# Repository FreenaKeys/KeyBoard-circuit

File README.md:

# キーボードの回路図

このリポジトリには自作キーボードの回路図データが含まれています。

## ファイル構成
- `schematic/` : 回路図ファイル (KiCad)
- `pcb/` : 基板データ
- `README.md` : この説明ファイル

## 使用方法
1. KiCad で `schematic/keyboard.sch` を開く  
2. 必要に応じて編集・出力する  

## ライセンス
今のところはありません

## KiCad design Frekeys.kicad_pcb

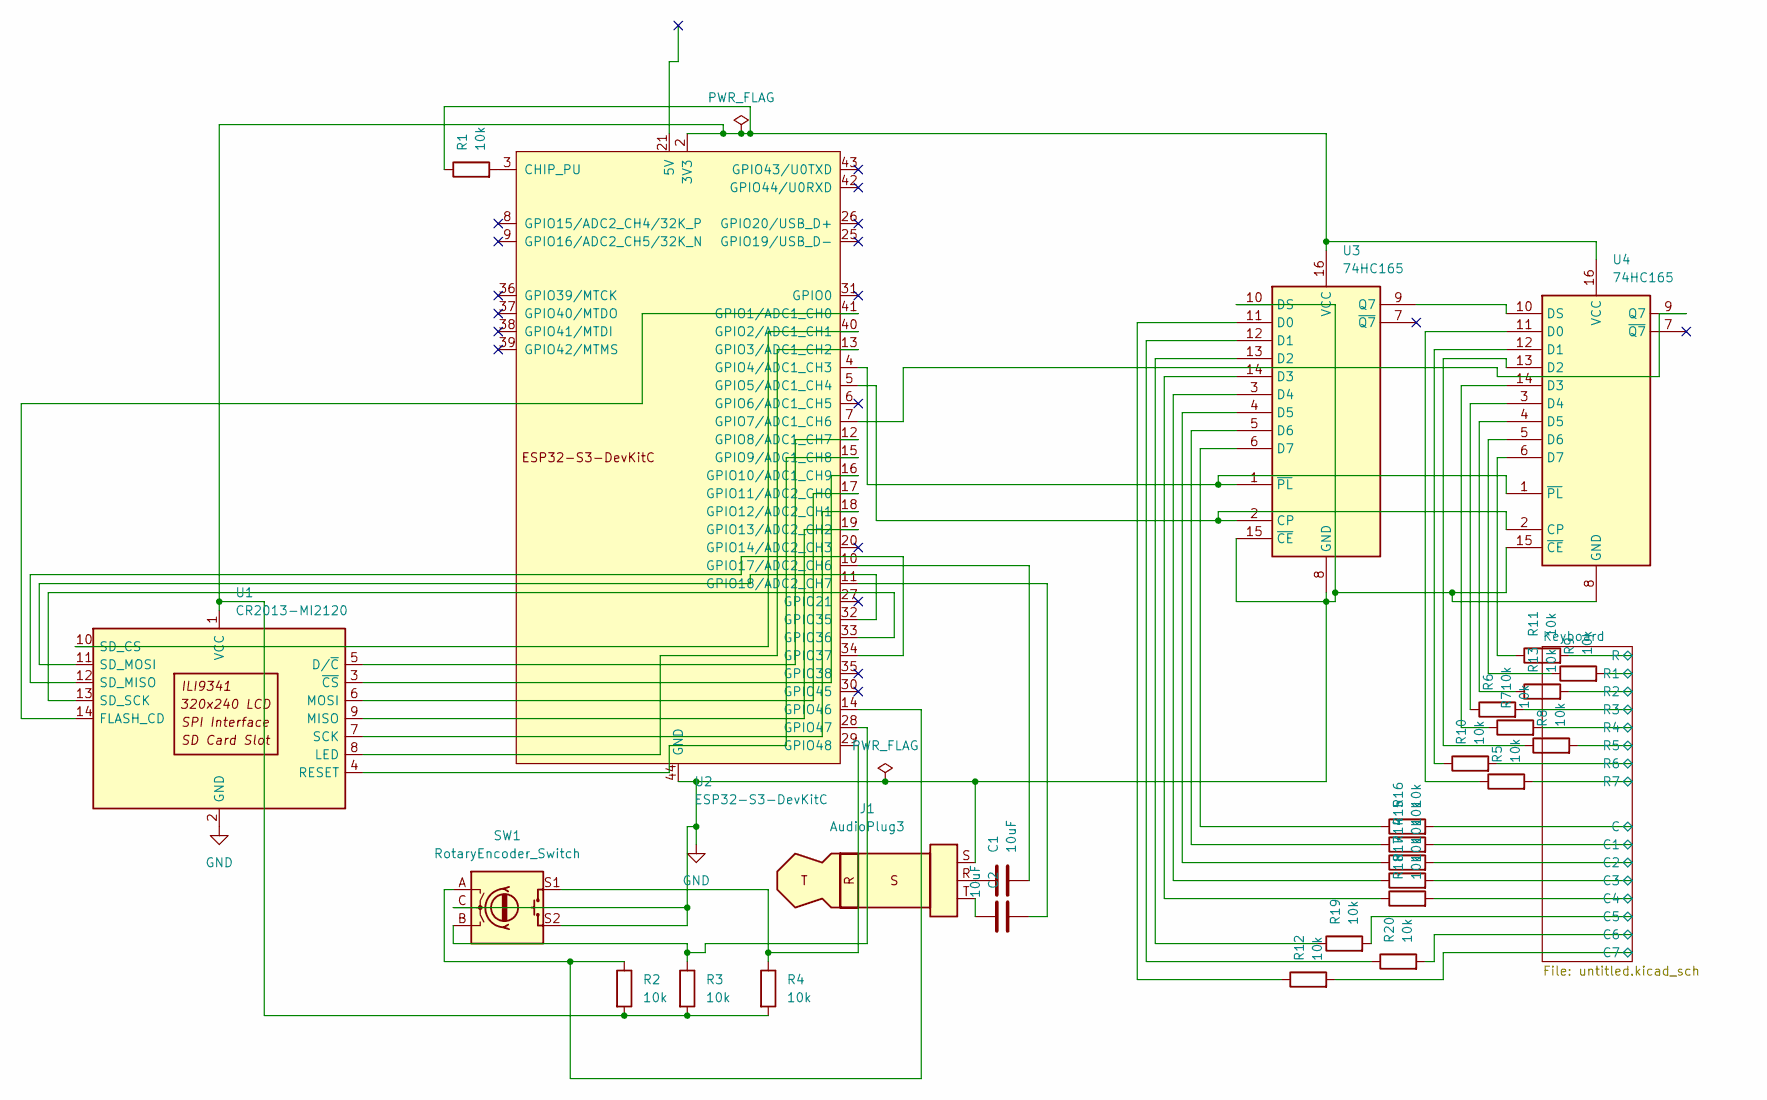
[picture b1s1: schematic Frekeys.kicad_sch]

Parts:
C1, C2: 10uF; C_0805_2012Metric
J1: AudioPlug3; Jack_3.5mm_CUI_SJ1-3523N_Horizontal
R1, R2, R3, R4, R5, R6, R7, R8, R9, R10, R11, R12, R13, R14, R15, R16, R17, R18, R19, R20: 10k; R_0805_2012Metric
SW1: RotaryEncoder_Switch; RotaryEncoder_Bourns_Vertical_PEC12R-3x17F-Sxxxx
U1: CR2013-MI2120
U2: ESP32-S3-DevKitC
U3, U4: 74HC165; SOIC-16_3.9x9.9mm_P1.27mm

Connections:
/Keyboard/C: R16.2; also elsewhere on the board
/Keyboard/C1: R15.2; also elsewhere on the board
/Keyboard/C2: R14.2; also elsewhere on the board
/Keyboard/C3: R17.2; also elsewhere on the board
/Keyboard/C4: R18.2; also elsewhere on the board
/Keyboard/C5: R19.2; also elsewhere on the board
/Keyboard/C6: R20.2; also elsewhere on the board
/Keyboard/C7: R12.2; also elsewhere on the board
/Keyboard/R: R11.2; also elsewhere on the board
/Keyboard/R1: R9.2; also elsewhere on the board
/Keyboard/R2: R13.2; also elsewhere on the board
/Keyboard/R3: R6.2; also elsewhere on the board
/Keyboard/R4: R7.2; also elsewhere on the board
/Keyboard/R5: R8.2; also elsewhere on the board
/Keyboard/R6: R10.2; also elsewhere on the board
/Keyboard/R7: R5.2; also elsewhere on the board
GND: J1.S, SW1.C, SW1.S2, U1.2 (GND), U2.22 (GND), U2.23 (GND), U2.24 (GND), U2.44 (GND), U3.8 (GND), U3.10 (DS), U3.15 (~CE), U4.8 (GND), U4.15 (~CE)
unnamed: C1.1, J1.R
unnamed: C2.1, J1.T
unnamed: U1.5 (D/~C), U2.12 (GPIO8/ADC1_CH7)
unnamed: U1.14 (FLASH_CD), U2.41 (GPIO1/ADC1_CH0)
unnamed: U1.8 (LED), U2.13 (GPIO3/ADC1_CH2)
unnamed: U1.9 (MISO), U2.19 (GPIO13/ADC2_CH2)
unnamed: U1.6 (MOSI), U2.17 (GPIO11/ADC2_CH0)
unnamed: U1.4 (RESET), U2.15 (GPIO9/ADC1_CH8)
unnamed: U1.7 (SCK), U2.18 (GPIO12/ADC2_CH1)
unnamed: U1.10 (SD_CS), U2.40 (GPIO2/ADC1_CH1)
unnamed: U1.12 (SD_MISO), U2.34 (GPIO37)
unnamed: U1.11 (SD_MOSI), U2.32 (GPIO35)
unnamed: U1.13 (SD_SCK), U2.33 (GPIO36)
unnamed: R1.1, R2.2, R3.2, R4.2, U1.1 (VCC), U2.1 (3V3), U2.2 (3V3), U3.16 (VCC), U4.16 (VCC)
unnamed: U1.3 (~CS), U2.16 (GPIO10/ADC1_CH9)
unnamed: R1.2, U2.3 (CHIP_PU)
unnamed: U2.4 (GPIO4/ADC1_CH3), U3.1 (~PL), U4.1 (~PL)
unnamed: U2.5 (GPIO5/ADC1_CH4), U3.2 (CP), U4.2 (CP)
unnamed: U2.7 (GPIO7/ADC1_CH6), U4.9 (Q7)
unnamed: C1.2, U2.10 (GPIO17/ADC2_CH6)
unnamed: C2.2, U2.11 (GPIO18/ADC2_CH7)
unnamed: R2.1, SW1.A, U2.14 (GPIO46)
unnamed: R3.1, SW1.B, U2.28 (GPIO47)
unnamed: R4.1, SW1.S1, U2.29 (GPIO48)
unnamed: R12.1, U3.11 (D0)
unnamed: R20.1, U3.12 (D1)
unnamed: R19.1, U3.13 (D2)
unnamed: R18.1, U3.14 (D3)
unnamed: R17.1, U3.3 (D4)
unnamed: R14.1, U3.4 (D5)
unnamed: R15.1, U3.5 (D6)
unnamed: R16.1, U3.6 (D7)
unnamed: U3.9 (Q7), U4.10 (DS)
unnamed: R5.1, U4.11 (D0)
unnamed: R10.1, U4.12 (D1)
unnamed: R8.1, U4.13 (D2)
unnamed: R7.1, U4.14 (D3)
unnamed: R6.1, U4.3 (D4)
unnamed: R13.1, U4.4 (D5)
unnamed: R9.1, U4.5 (D6)
unnamed: R11.1, U4.6 (D7)

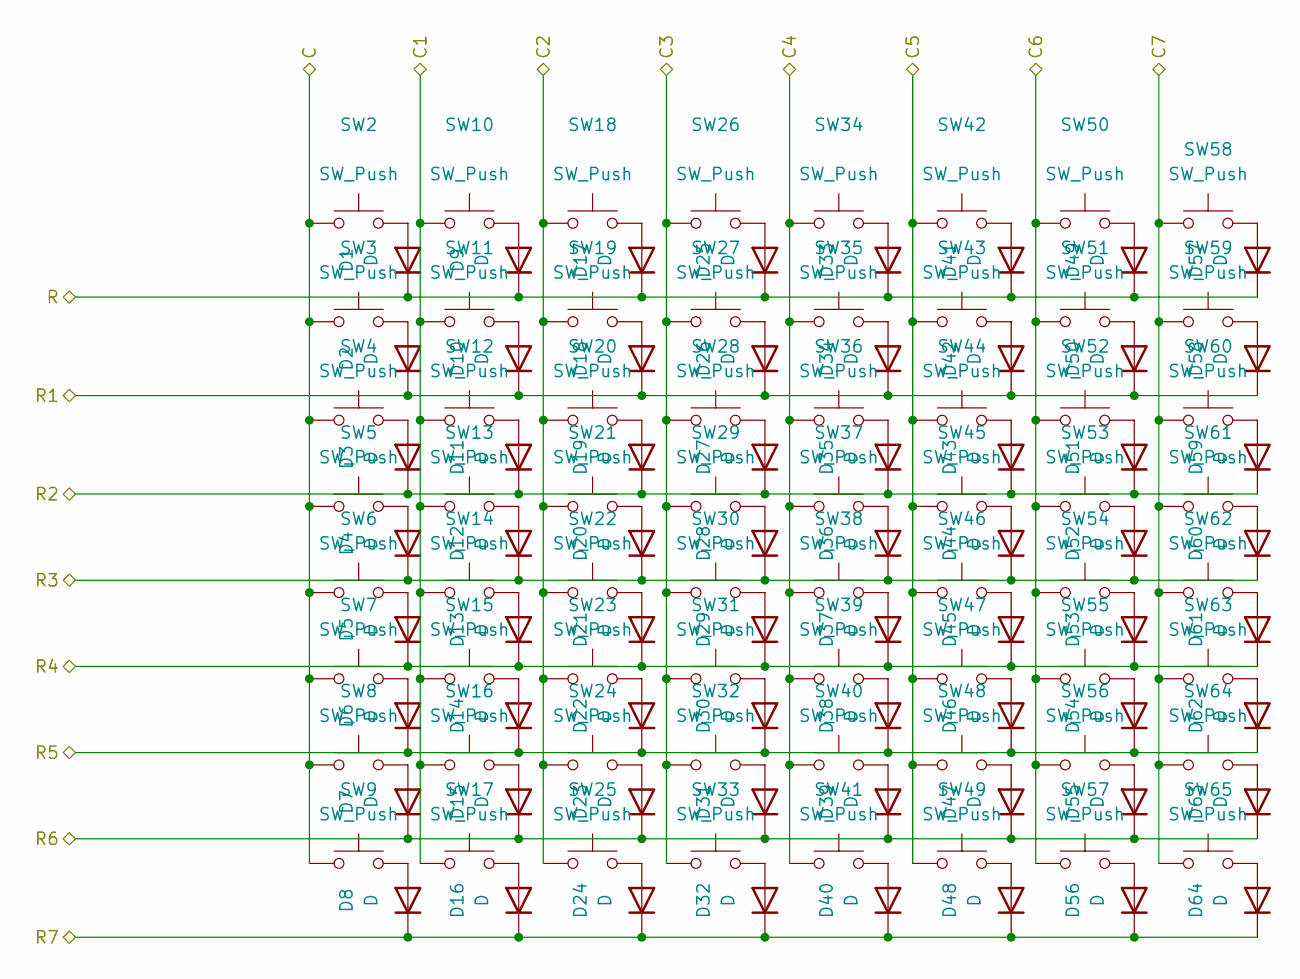
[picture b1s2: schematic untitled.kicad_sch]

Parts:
D1, D2, D3, D4, D5, D6, D7, D8, D9, D10, D11, D12, D13, D14, D15, D16, D17, D18, D19, D20, D21, D22, D23, D24, D25, D26, D27, D28, D29, D30, D31, D32, D33, D34, D35, D36, D37, D38, D39, D40, D41, D42, D43, D44, D45, D46, D47, D48, D49, D50, D51, D52, D53, D54, D55, D56, D57, D58, D59, D60, D61, D62, D63, D64: D; D_0805_2012Metric
SW2, SW7, SW8, SW9, SW10, SW11, SW12, SW13, SW15, SW16, SW17, SW18, SW19, SW20, SW21, SW23, SW24, SW25, SW26, SW27, SW28, SW29, SW30, SW31, SW32, SW33, SW34, SW35, SW36, SW37, SW39, SW40, SW41, SW42, SW43, SW44, SW45, SW46, SW47, SW48, SW49, SW50, SW51, SW52, SW53, SW54, SW55, SW56, SW57, SW58, SW59, SW60, SW61, SW62, SW65: SW_Push; SW_Hotswap_Kailh_MX_1.00u
SW3: SW_Push; SW_Hotswap_Kailh_MX_1.50u
SW4: SW_Push; SW_Hotswap_Kailh_MX_1.75u
SW5, SW63: SW_Push; SW_Hotswap_Kailh_MX_2.00u
SW6, SW14, SW22: SW_Push; SW_Hotswap_Kailh_MX_1.25u
SW38: SW_Push; SW_Hotswap_Kailh_MX_6.25u
SW64: SW_Push; SW_Hotswap_Kailh_MX_ISOEnter

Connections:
/Keyboard/C: SW2.1, SW3.1, SW4.1, SW5.1, SW6.1, SW7.1, SW8.1, SW9.1; also elsewhere on the board
/Keyboard/C1: SW10.1, SW11.1, SW12.1, SW13.1, SW14.1, SW15.1, SW16.1, SW17.1; also elsewhere on the board
/Keyboard/C2: SW18.1, SW19.1, SW20.1, SW21.1, SW22.1, SW23.1, SW24.1, SW25.1; also elsewhere on the board
/Keyboard/C3: SW26.1, SW27.1, SW28.1, SW29.1, SW30.1, SW31.1, SW32.1, SW33.1; also elsewhere on the board
/Keyboard/C4: SW34.1, SW35.1, SW36.1, SW37.1, SW38.1, SW39.1, SW40.1, SW41.1; also elsewhere on the board
/Keyboard/C5: SW42.1, SW43.1, SW44.1, SW45.1, SW46.1, SW47.1, SW48.1, SW49.1; also elsewhere on the board
/Keyboard/C6: SW50.1, SW51.1, SW52.1, SW53.1, SW54.1, SW55.1, SW56.1, SW57.1; also elsewhere on the board
/Keyboard/C7: SW58.1, SW59.1, SW60.1, SW61.1, SW62.1, SW63.1, SW64.1, SW65.1; also elsewhere on the board
/Keyboard/R: D1.1 (K), D9.1 (K), D17.1 (K), D25.1 (K), D33.1 (K), D41.1 (K), D49.1 (K), D57.1 (K); also elsewhere on the board
/Keyboard/R1: D2.1 (K), D10.1 (K), D18.1 (K), D26.1 (K), D34.1 (K), D42.1 (K), D50.1 (K), D58.1 (K); also elsewhere on the board
/Keyboard/R2: D3.1 (K), D11.1 (K), D19.1 (K), D27.1 (K), D35.1 (K), D43.1 (K), D51.1 (K), D59.1 (K); also elsewhere on the board
/Keyboard/R3: D4.1 (K), D12.1 (K), D20.1 (K), D28.1 (K), D36.1 (K), D44.1 (K), D52.1 (K), D60.1 (K); also elsewhere on the board
/Keyboard/R4: D5.1 (K), D13.1 (K), D21.1 (K), D29.1 (K), D37.1 (K), D45.1 (K), D53.1 (K), D61.1 (K); also elsewhere on the board
/Keyboard/R5: D6.1 (K), D14.1 (K), D22.1 (K), D30.1 (K), D38.1 (K), D46.1 (K), D54.1 (K), D62.1 (K); also elsewhere on the board
/Keyboard/R6: D7.1 (K), D15.1 (K), D23.1 (K), D31.1 (K), D39.1 (K), D47.1 (K), D55.1 (K), D63.1 (K); also elsewhere on the board
/Keyboard/R7: D8.1 (K), D16.1 (K), D24.1 (K), D32.1 (K), D40.1 (K), D48.1 (K), D56.1 (K), D64.1 (K); also elsewhere on the board
unnamed: D1.2 (A), SW2.2
unnamed: D2.2 (A), SW3.2
unnamed: D3.2 (A), SW4.2
unnamed: D4.2 (A), SW5.2
unnamed: D5.2 (A), SW6.2
unnamed: D6.2 (A), SW7.2
unnamed: D7.2 (A), SW8.2
unnamed: D8.2 (A), SW9.2
unnamed: D9.2 (A), SW10.2
unnamed: D10.2 (A), SW11.2
unnamed: D11.2 (A), SW12.2
unnamed: D12.2 (A), SW13.2
unnamed: D13.2 (A), SW14.2
unnamed: D14.2 (A), SW15.2
unnamed: D15.2 (A), SW16.2
unnamed: D16.2 (A), SW17.2
unnamed: D17.2 (A), SW18.2
unnamed: D18.2 (A), SW19.2
unnamed: D19.2 (A), SW20.2
unnamed: D20.2 (A), SW21.2
unnamed: D21.2 (A), SW22.2
unnamed: D22.2 (A), SW23.2
unnamed: D23.2 (A), SW24.2
unnamed: D24.2 (A), SW25.2
unnamed: D25.2 (A), SW26.2
unnamed: D26.2 (A), SW27.2
unnamed: D27.2 (A), SW28.2
unnamed: D28.2 (A), SW29.2
unnamed: D29.2 (A), SW30.2
unnamed: D30.2 (A), SW31.2
unnamed: D31.2 (A), SW32.2
unnamed: D32.2 (A), SW33.2
unnamed: D33.2 (A), SW34.2
unnamed: D34.2 (A), SW35.2
unnamed: D35.2 (A), SW36.2
unnamed: D36.2 (A), SW37.2
unnamed: D37.2 (A), SW38.2
unnamed: D38.2 (A), SW39.2
unnamed: D39.2 (A), SW40.2
unnamed: D40.2 (A), SW41.2
unnamed: D41.2 (A), SW42.2
unnamed: D42.2 (A), SW43.2
unnamed: D43.2 (A), SW44.2
unnamed: D44.2 (A), SW45.2
unnamed: D45.2 (A), SW46.2
unnamed: D46.2 (A), SW47.2
unnamed: D47.2 (A), SW48.2
unnamed: D48.2 (A), SW49.2
unnamed: D49.2 (A), SW50.2
unnamed: D50.2 (A), SW51.2
unnamed: D51.2 (A), SW52.2
unnamed: D52.2 (A), SW53.2
unnamed: D53.2 (A), SW54.2
unnamed: D54.2 (A), SW55.2
unnamed: D55.2 (A), SW56.2
unnamed: D56.2 (A), SW57.2
unnamed: D57.2 (A), SW58.2
unnamed: D58.2 (A), SW59.2
unnamed: D59.2 (A), SW60.2
unnamed: D60.2 (A), SW61.2
unnamed: D61.2 (A), SW62.2
unnamed: D62.2 (A), SW63.2
unnamed: D63.2 (A), SW64.2
unnamed: D64.2 (A), SW65.2

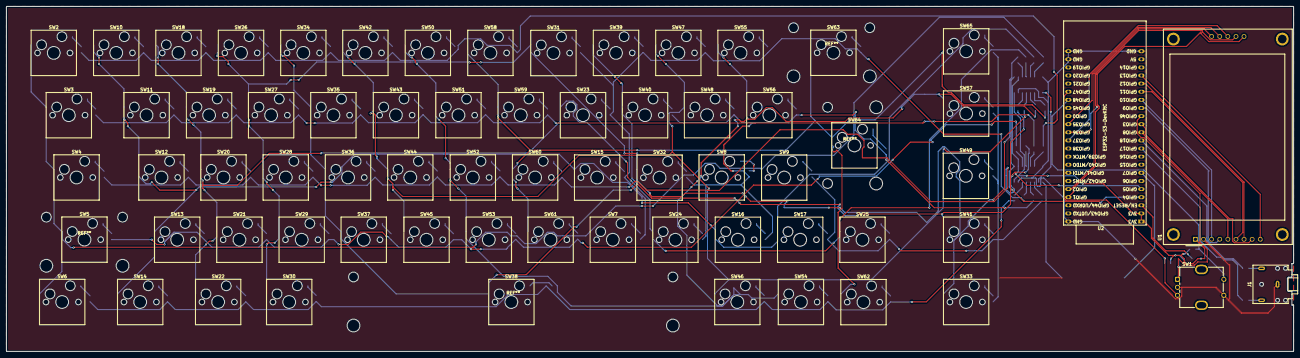
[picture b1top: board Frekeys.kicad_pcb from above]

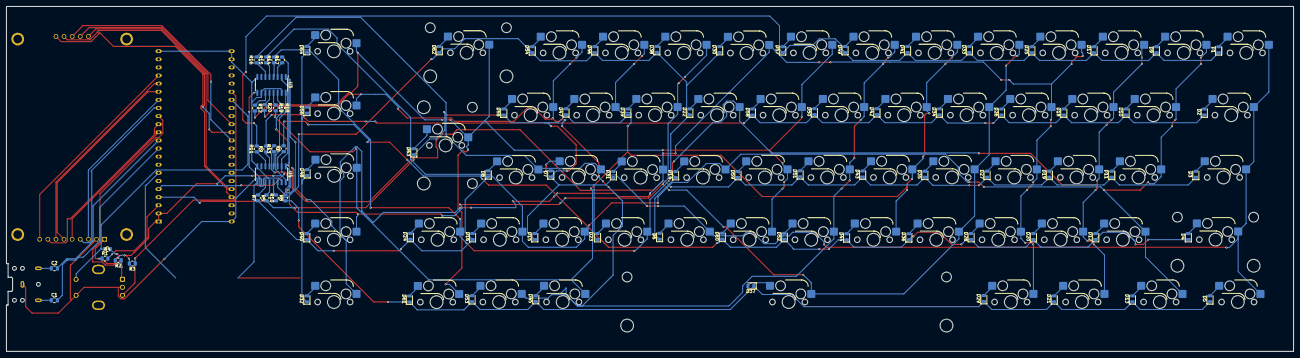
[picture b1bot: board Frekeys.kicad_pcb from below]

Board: 2 copper layers, 403.0 x 108.0 mm, 156 parts (88 on the bottom side), 122 nets.

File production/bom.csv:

Designator,Footprint,Quantity,Value,LCSC Part #
"C1, C2",0805,2,10uF,
"D1, D10, D11, D12, D13, D14, D15, D16, D17, D18, D19, D2, D20, D21, D22, D23, D24, D25, D26, D27, D28, D29, D3, D30, D31, D32, D33, D34, D35, D36, D37, D38, D39, D4, D40, D41, D42, D43, D44, D45, D46, D47, D48, D49, D5, D50, D51, D52, D53, D54, D55, D56, D57, D58, D59, D6, D60, D61, D62, D63, D64, D7, D8, D9",0805,64,D,
J1,Jack_3.5mm_CUI_SJ1-3523N_Horizontal,1,AudioPlug3,
"R1, R10, R11, R12, R13, R14, R15, R16, R17, R18, R19, R2, R20, R3, R4, R5, R6, R7, R8, R9",0805,20,10k,
SW1,RotaryEncoder_Bourns_Vertical_PEC12R-3x17F-Sxxxx,1,RotaryEncoder_Switch,
"SW10, SW11, SW12, SW13, SW15, SW16, SW17, SW18, SW19, SW2, SW20, SW21, SW23, SW24, SW25, SW26, SW27, SW28, SW29, SW30, SW31, SW32, SW33, SW34, SW35, SW36, SW37, SW39, SW40, SW41, SW42, SW43, SW44, SW45, SW46, SW47, SW48, SW49, SW50, SW51, SW52, SW53, SW54, SW55, SW56, SW57, SW58, SW59, SW60, SW61, SW62, SW65, SW7, SW8, SW9",SW_Hotswap_Kailh_MX_1.00u,55,SW_Push,
"SW14, SW22, SW6",SW_Hotswap_Kailh_MX_1.25u,3,SW_Push,
SW3,SW_Hotswap_Kailh_MX_1.50u,1,SW_Push,
SW38,SW_Hotswap_Kailh_MX_6.25u,1,SW_Push,
SW4,SW_Hotswap_Kailh_MX_1.75u,1,SW_Push,
"SW5, SW63",SW_Hotswap_Kailh_MX_2.00u,2,SW_Push,
SW64,SW_Hotswap_Kailh_MX_ISOEnter,1,SW_Push,
U1,CR2013-MI2120,1,CR2013-MI2120,
U2,ESP32-S3-DevKitC,1,ESP32-S3-DevKitC,
"U3, U4",SOIC-16_3.9x9.9mm_P1.27mm,2,74HC165,

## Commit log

2025-08-27 Making...
2025-09-03 Making.. 2
2025-09-04 making.... 3
    making.... 3
2025-09-04 Update Frekeys.kicad_pcb
    Nope comment
2025-09-04 ignorep
2025-09-04 a
    a
2025-09-04 ダイオードの場所設定OK
2025-09-05 形状ほぼ完成
2025-09-05 Maybe Final
2025-09-08 maybe final
    maybe final
2025-09-09 Final Commit
